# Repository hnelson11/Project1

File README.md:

# Project1_IRKeyboard

Theory Documentation : Advanced PCB Layout

## Purpose:

The Infrared Keyboard is used as a first printed circuit board creation project. 
The Infrared Keyboard will allow infrared light to transmit data to a personal computer rather than transmitting through a traditional hardwired connection.
This keyboard will utilize the Attiny85-20SU microcontroller, USB power 10119194-001LF, and infrared receiver vs1838b.

## How does it work?

As stated above the Infrared Keyboard will allow infrared light to transmit data to a personal computer rather than transmitting through a traditional hardwired connection.
The ATtiny85 will control the IR receiver's input and output through the RCV LED shown in the IR_Schematic. 
The RCV LED will turn on when a signal is received from the receiver. 
Similarly, a PWR LED will be 

## Electrical Connections:

All pinnout connections within this schematic have been made according to component data sheets made in the reference section below. 
Voltage input and ground connections are connected properly to the ATtiny85, which is shown on page 2 of the ATtiny85 data sheet.
The USB2.0 voltage and ground connections are shown on page 1 of the USB2.0 data sheet, and the IR receiver voltage and ground connections are found on page 1 through 3 of the vs1838b data sheet.
Any additional electrical component connections to ground and voltage input are connected properly according to part specification. 
The ATtiny85 has connections to the USB connector through the D- and D+ pins of the USB. 
The D- pin should be connected to the PB3 pinnout of the ATtin85, which is the CLK1.
The D+ pin should be connected to the ATtiny85 PB4 pin, which is CLK 0. 
The IR receiver will be connected to the PB1 pin of the ATtiny85, which is the MISO connection. 
This pinnout willl allow the microcontroller to receive the data that is being transmitted from the IR receiver.
Shunt Capacitors are connected to pin 8, Vcc pin of the ATtiny85, to prevent high frequency voltage spikes.
Additionally the reset pin is set to pin 8 of the ATtiny85 to set the reset pin as high.

## Programmer:

While programming the ATtiny85, use the IR2USB_Keyboard.ino and the IR2USB_Serial.ino found on Stefan Wagner's github repository listed in reference below.
Pins that need to be programmed through arduino or the Analog Discovery2 are as listed: PB5, PB3, PB4, and PB2. 
The PB1 pin will be connected to the IR receiver, the PB0 pin will be connected to the PWR LED, pin 8 will connect to Vcc, and pin 4 will connect to GND.
Please make sure you BURN THE BOOTLOADER!
You want your ATtiny85 to have code if it is a SMT component.

### Side note:

The ATtiny85 will be in control of the keyboard, so its placement was made towards the middle of the schematic / PCB due to preference.
This is shown through the IRKeyboard_Schematic, as well as much of the rest of the schematic was placed in the correct orientation as will be placed in the PCB.
Voltage concerns should not be an issue, because the maximum voltage that the IR receiver can withstand is 5.5V and the minimum voltage is 2.7V.
The voltage connected to the ATtiny85 will be 5V.
To ensure that voltage entering the ATtiny85 remains at 5V and not larger, 3.6V voltage regulators will be placed near the PB3 and PB4 pins of the ATtiny85 to act as voltage regulators for the board.
These zener diodes are able to ensure that the microcontroller can fully run on 5V power as they limit the USB voltage output.
Also please ensure that the voltage used during testing purposes is limited to 5V, and that all electrical component (i.e. Diodes, Capacitors, etc...) are placed in the correct orientation for current flow.
ALSO DOWNLOAD DIGIKEY X KICAD LIBRARY!!

## References:

- [Stefan Wagner Git](https://github.com/wagiminator)
- [IR2USB Wiring](https://raw.githubusercontent.com/wagiminator/ATtiny85-IR2USB/main/documentation/IR2USB_wiring.png)
- [IR2USB Repository](https://github.com/wagiminator/ATtiny85-IR2USB/commit/2459adeddc2d69f14432a9166a96c19850a03573) - Arduino code
- [VUSB](https://www.obdev.at/products/vusb/index.html) - VUSB Libary for Arduino
- [ATtiny85 Data Sheet](https://www.mouser.com/datasheet/2/268/Atmel_2586_AVR_8_bit_Microcontroller_ATtiny25_ATti-1315542.pdf)
- [IR Receiver Datasheet](http://eeshop.unl.edu/pdf/VS1838-Infrared-Receiver-datasheet.pdf)
- [USB Datasheet](https://www.amphenol-cs.com/media/wysiwyg/files/drawing/10118194.pdf)

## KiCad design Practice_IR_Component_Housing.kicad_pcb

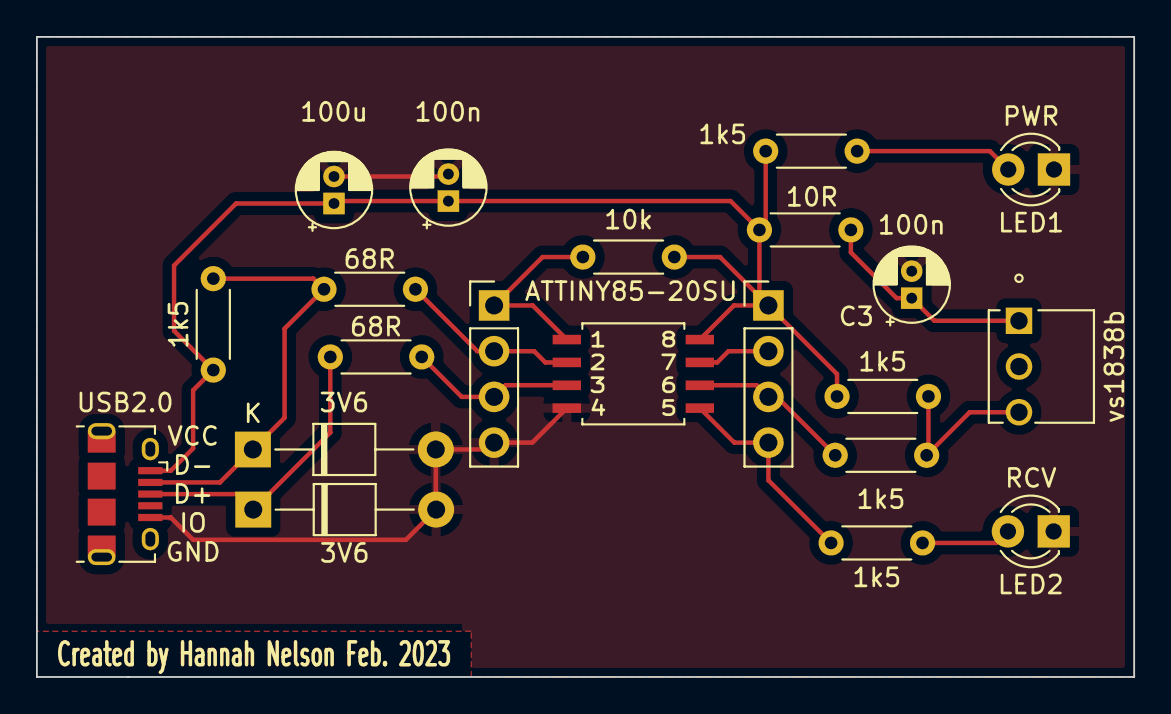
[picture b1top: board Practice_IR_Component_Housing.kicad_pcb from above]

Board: 2 copper layers, 61.0 x 35.6 mm, 19 parts (0 on the bottom side), 13 nets.

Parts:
C1: 100u; CP_Radial_D4.0mm_P1.50mm
C2, C3: 100n; CP_Radial_D4.0mm_P1.50mm
D1, D2: 3V6; D_T-1_P10.16mm_Horizontal
IC1: ATTINY85-20SU
IR1: vs1838b; TSOP34438
LED1: PWR; LED_D3.0mm
LED2: RCV; LED_D3.0mm
R1: 10k; R_Axial_DIN0204_L3.6mm_D1.6mm_P5.08mm_Horizontal
R2, R5, R6, R8, R9: 1k5; R_Axial_DIN0204_L3.6mm_D1.6mm_P5.08mm_Horizontal
R3, R4: 68R; R_Axial_DIN0204_L3.6mm_D1.6mm_P5.08mm_Horizontal
R7: 10R; R_Axial_DIN0204_L3.6mm_D1.6mm_P5.08mm_Horizontal
USB2.0: 10118194-0001LF; USB_Micro-B_Amphenol_10118194_Horizontal

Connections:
GND: C1.2, C2.2, C3.2, D1.2 (A), D2.2 (A), IC1.4 (GND), LED1.1 (K), LED2.1 (K), USB2.0.GND
unnamed: C3.1, IR1.V+, R7.1
unnamed: IC1.1 (PB5), R1.2
unnamed: IC1.2 (PB3), R4.2
unnamed: IC1.3 (PB4), R3.2
unnamed: IC1.5 (PB0), R6.1
unnamed: IC1.6 (PB1), R8.2
unnamed: IR1.OUT, R8.1, R9.1
unnamed: LED1.2 (A), R2.2
unnamed: LED2.2 (A), R6.2
unnamed: D1.1 (K), R3.1, USB2.0.D+
unnamed: D2.1 (K), R4.1, R5.1, USB2.0.D-
VCC: C1.1, C2.1, IC1.8 (VCC), R1.1, R2.1, R5.2, R7.2, R9.2, USB2.0.VCC

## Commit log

2023-02-13 Create PCB_Layout_Constraints
2023-02-13 Update PCB_Layout_Constraints
2023-02-14 Create External_Design_Review_Report
2023-02-14 Rename External_Design_Review_Report to Schematic_External_Design_Review_Report
2023-02-14 Create PCB_External_Design_Review_Report
2023-02-14 README: vertical space between sections
2023-02-14 README: promote headings
2023-02-14 README: no space in link syntax
2023-02-20 Shift text, OSH Park order version
2023-02-21 Final PCB Layout Constraints
2023-02-21 In Progress

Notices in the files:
parts and their libraries:
Copyright 2021 Accelerated Designs. All rights reserved.
